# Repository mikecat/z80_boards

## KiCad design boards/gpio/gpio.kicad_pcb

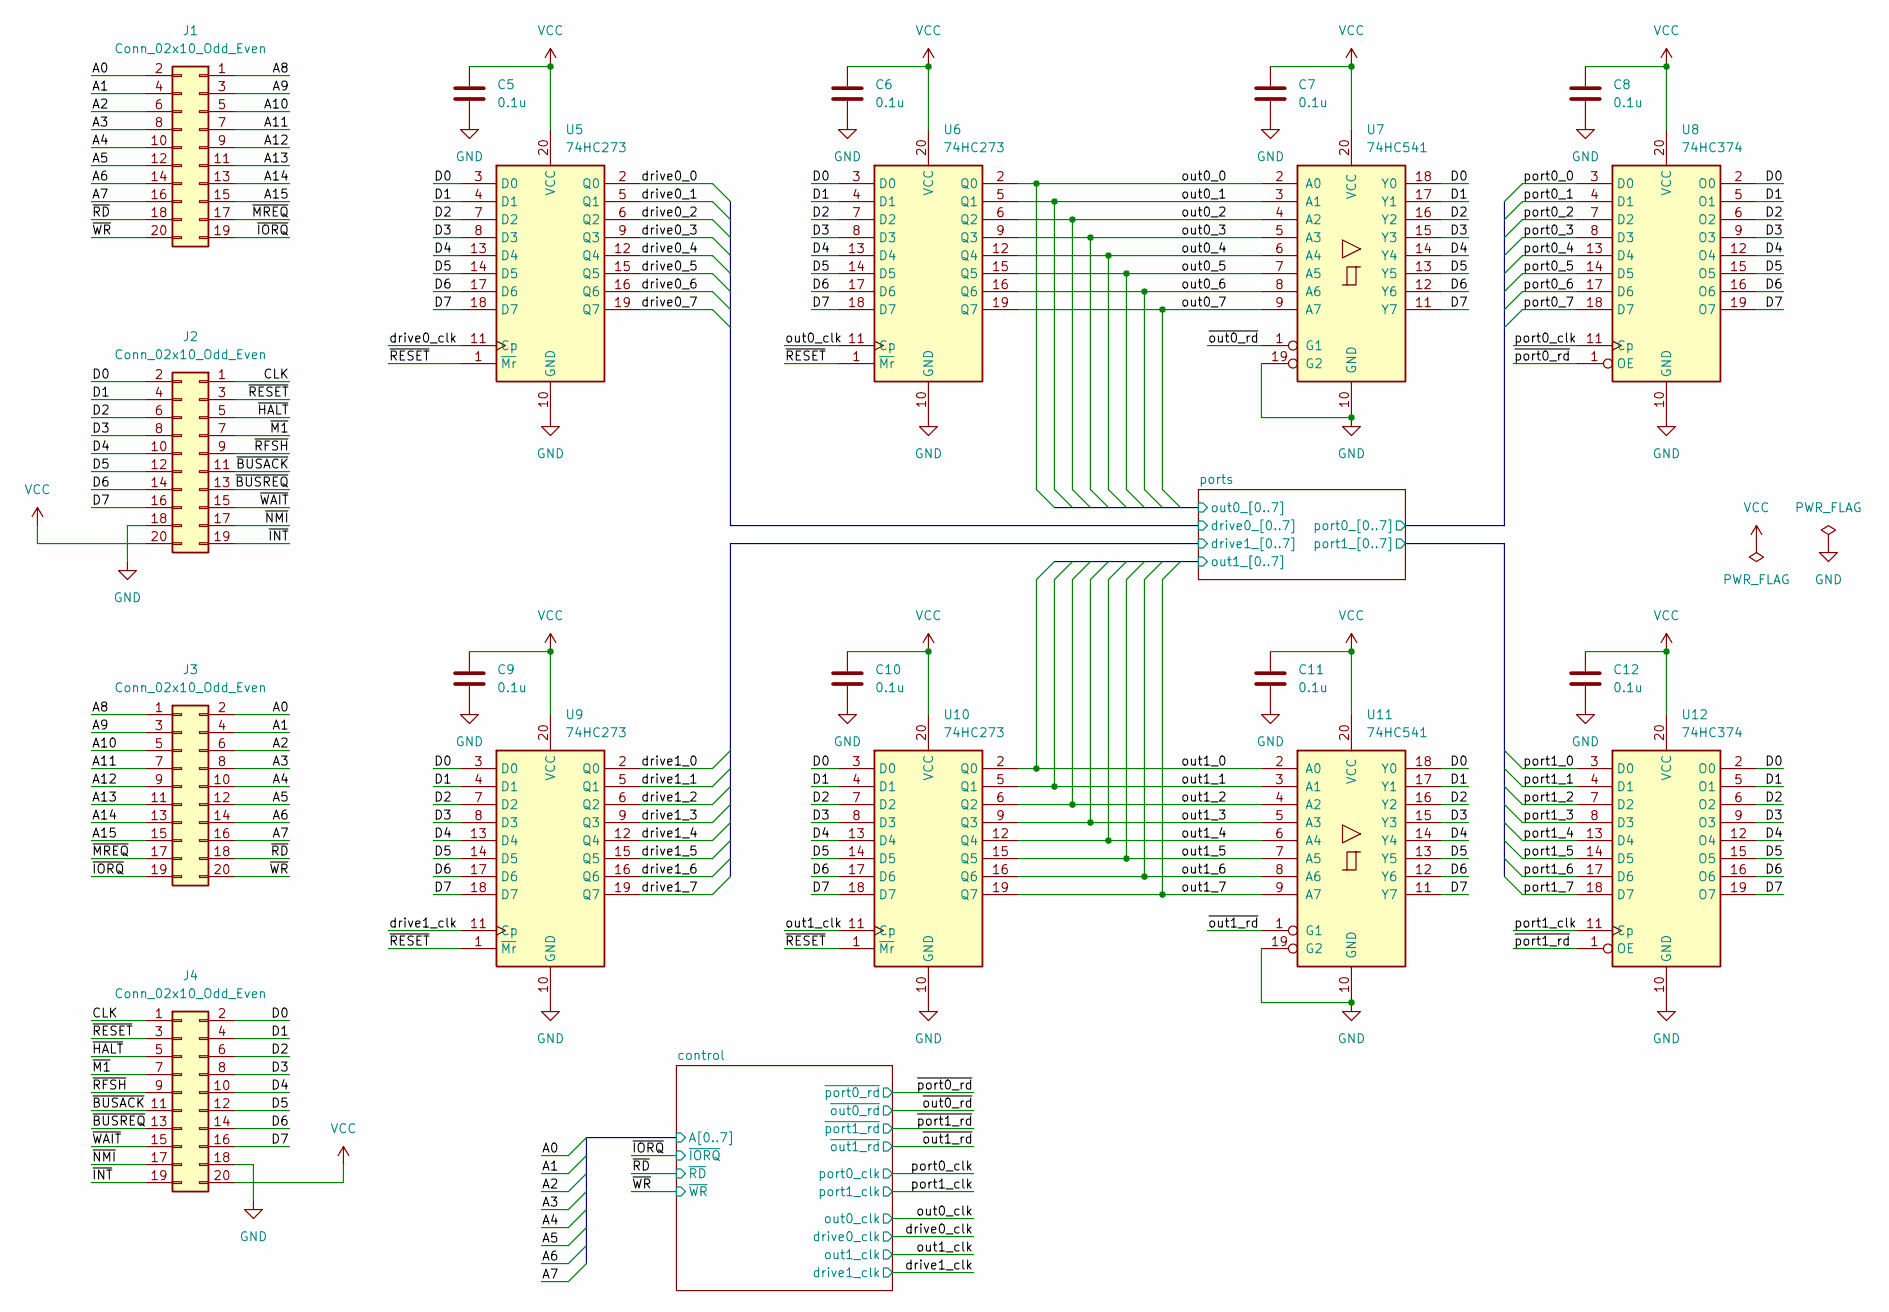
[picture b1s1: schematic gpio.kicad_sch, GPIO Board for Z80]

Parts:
C5, C6, C7, C8, C9, C10, C11, C12: 0.1u; C_0805_2012Metric_Pad1.18x1.45mm_HandSolder
J1, J2: Conn_02x10_Odd_Even; PinSocket_2x10_P2.54mm_Vertical
J3, J4: Conn_02x10_Odd_Even; PinHeader_2x10_P2.54mm_Vertical
U5, U6, U9, U10: 74HC273; DIP-20_W7.62mm
U7, U11: 74HC541; DIP-20_W7.62mm
U8, U12: 74HC374; DIP-20_W7.62mm

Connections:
/A8: J1.1, J3.1
/A9: J1.3, J3.3
/A10: J1.5, J3.5
/A11: J1.7, J3.7
/A12: J1.9, J3.9
/A13: J1.11, J3.11
/A14: J1.13, J3.13
/A15: J1.15, J3.15
/CLK: J2.1, J4.1
/D0: J2.2, J4.2, U5.3 (D0), U6.3 (D0), U7.18 (Y0), U8.2 (O0), U9.3 (D0), U10.3 (D0), U11.18 (Y0), U12.2 (O0)
/D1: J2.4, J4.4, U5.4 (D1), U6.4 (D1), U7.17 (Y1), U8.5 (O1), U9.4 (D1), U10.4 (D1), U11.17 (Y1), U12.5 (O1)
/D2: J2.6, J4.6, U5.7 (D2), U6.7 (D2), U7.16 (Y2), U8.6 (O2), U9.7 (D2), U10.7 (D2), U11.16 (Y2), U12.6 (O2)
/D3: J2.8, J4.8, U5.8 (D3), U6.8 (D3), U7.15 (Y3), U8.9 (O3), U9.8 (D3), U10.8 (D3), U11.15 (Y3), U12.9 (O3)
/D4: J2.10, J4.10, U5.13 (D4), U6.13 (D4), U7.14 (Y4), U8.12 (O4), U9.13 (D4), U10.13 (D4), U11.14 (Y4), U12.12 (O4)
/D5: J2.12, J4.12, U5.14 (D5), U6.14 (D5), U7.13 (Y5), U8.15 (O5), U9.14 (D5), U10.14 (D5), U11.13 (Y5), U12.15 (O5)
/D6: J2.14, J4.14, U5.17 (D6), U6.17 (D6), U7.12 (Y6), U8.16 (O6), U9.17 (D6), U10.17 (D6), U11.12 (Y6), U12.16 (O6)
/D7: J2.16, J4.16, U5.18 (D7), U6.18 (D7), U7.11 (Y7), U8.19 (O7), U9.18 (D7), U10.18 (D7), U11.11 (Y7), U12.19 (O7)
/control/A0: J1.2, J3.2; also elsewhere on the board
/control/A1: J1.4, J3.4; also elsewhere on the board
/control/A2: J1.6, J3.6; also elsewhere on the board
/control/A3: J1.8, J3.8; also elsewhere on the board
/control/A4: J1.10, J3.10; also elsewhere on the board
/control/A5: J1.12, J3.12; also elsewhere on the board
/control/A6: J1.14, J3.14; also elsewhere on the board
/control/A7: J1.16, J3.16; also elsewhere on the board
/drive0_clk: U5.11 (Cp); also elsewhere on the board
/drive1_clk: U9.11 (Cp); also elsewhere on the board
/out0_clk: U6.11 (Cp); also elsewhere on the board
/out1_clk: U10.11 (Cp); also elsewhere on the board
/port0_clk: U8.11 (Cp); also elsewhere on the board
/port1_clk: U12.11 (Cp); also elsewhere on the board
/ports/drive0_0: U5.2 (Q0); also elsewhere on the board
/ports/drive0_1: U5.5 (Q1); also elsewhere on the board
/ports/drive0_2: U5.6 (Q2); also elsewhere on the board
/ports/drive0_3: U5.9 (Q3); also elsewhere on the board
/ports/drive0_4: U5.12 (Q4); also elsewhere on the board
/ports/drive0_5: U5.15 (Q5); also elsewhere on the board
/ports/drive0_6: U5.16 (Q6); also elsewhere on the board
/ports/drive0_7: U5.19 (Q7); also elsewhere on the board
/ports/drive1_0: U9.2 (Q0); also elsewhere on the board
/ports/drive1_1: U9.5 (Q1); also elsewhere on the board
/ports/drive1_2: U9.6 (Q2); also elsewhere on the board
/ports/drive1_3: U9.9 (Q3); also elsewhere on the board
/ports/drive1_4: U9.12 (Q4); also elsewhere on the board
/ports/drive1_5: U9.15 (Q5); also elsewhere on the board
/ports/drive1_6: U9.16 (Q6); also elsewhere on the board
/ports/drive1_7: U9.19 (Q7); also elsewhere on the board
/ports/out0_0: U6.2 (Q0), U7.2 (A0); also elsewhere on the board
/ports/out0_1: U6.5 (Q1), U7.3 (A1); also elsewhere on the board
/ports/out0_2: U6.6 (Q2), U7.4 (A2); also elsewhere on the board
/ports/out0_3: U6.9 (Q3), U7.5 (A3); also elsewhere on the board
/ports/out0_4: U6.12 (Q4), U7.6 (A4); also elsewhere on the board
/ports/out0_5: U6.15 (Q5), U7.7 (A5); also elsewhere on the board
/ports/out0_6: U6.16 (Q6), U7.8 (A6); also elsewhere on the board
/ports/out0_7: U6.19 (Q7), U7.9 (A7); also elsewhere on the board
/ports/out1_0: U10.2 (Q0), U11.2 (A0); also elsewhere on the board
/ports/out1_1: U10.5 (Q1), U11.3 (A1); also elsewhere on the board
/ports/out1_2: U10.6 (Q2), U11.4 (A2); also elsewhere on the board
/ports/out1_3: U10.9 (Q3), U11.5 (A3); also elsewhere on the board
/ports/out1_4: U10.12 (Q4), U11.6 (A4); also elsewhere on the board
/ports/out1_5: U10.15 (Q5), U11.7 (A5); also elsewhere on the board
/ports/out1_6: U10.16 (Q6), U11.8 (A6); also elsewhere on the board
/ports/out1_7: U10.19 (Q7), U11.9 (A7); also elsewhere on the board
/ports/port0_0: U8.3 (D0); also elsewhere on the board
/ports/port0_1: U8.4 (D1); also elsewhere on the board
/ports/port0_2: U8.7 (D2); also elsewhere on the board
/ports/port0_3: U8.8 (D3); also elsewhere on the board
/ports/port0_4: U8.13 (D4); also elsewhere on the board
/ports/port0_5: U8.14 (D5); also elsewhere on the board
/ports/port0_6: U8.17 (D6); also elsewhere on the board
/ports/port0_7: U8.18 (D7); also elsewhere on the board
/ports/port1_0: U12.3 (D0); also elsewhere on the board
/ports/port1_1: U12.4 (D1); also elsewhere on the board
/ports/port1_2: U12.7 (D2); also elsewhere on the board
/ports/port1_3: U12.8 (D3); also elsewhere on the board
/ports/port1_4: U12.13 (D4); also elsewhere on the board
/ports/port1_5: U12.14 (D5); also elsewhere on the board
/ports/port1_6: U12.17 (D6); also elsewhere on the board
/ports/port1_7: U12.18 (D7); also elsewhere on the board
/~BUSACK: J2.11, J4.11
/~BUSREQ: J2.13, J4.13
/~HALT: J2.5, J4.5
/~INT: J2.19, J4.19
/~IORQ: J1.19, J3.19; also elsewhere on the board
/~M1: J2.7, J4.7
/~MREQ: J1.17, J3.17
/~NMI: J2.17, J4.17
/~RD: J1.18, J3.18; also elsewhere on the board
/~RESET: J2.3, J4.3, U5.1 (~Mr), U6.1 (~Mr), U9.1 (~Mr), U10.1 (~Mr)
/~RFSH: J2.9, J4.9
/~WAIT: J2.15, J4.15
/~WR: J1.20, J3.20; also elsewhere on the board
/~out0_rd: U7.1 (G1); also elsewhere on the board
/~out1_rd: U11.1 (G1); also elsewhere on the board
/~port0_rd: U8.1 (OE); also elsewhere on the board
/~port1_rd: U12.1 (OE); also elsewhere on the board
GND: C5.2, C6.2, C7.2, C8.2, C9.2, C10.2, C11.2, C12.2, J2.18, J4.18, U5.10 (GND), U6.10 (GND), U7.10 (GND), U7.19 (G2), U8.10 (GND), U9.10 (GND), U10.10 (GND), U11.10 (GND), U11.19 (G2), U12.10 (GND); also elsewhere on the board
VCC: C5.1, C6.1, C7.1, C8.1, C9.1, C10.1, C11.1, C12.1, J2.20, J4.20, U5.20 (VCC), U6.20 (VCC), U7.20 (VCC), U8.20 (VCC), U9.20 (VCC), U10.20 (VCC), U11.20 (VCC), U12.20 (VCC); also elsewhere on the board

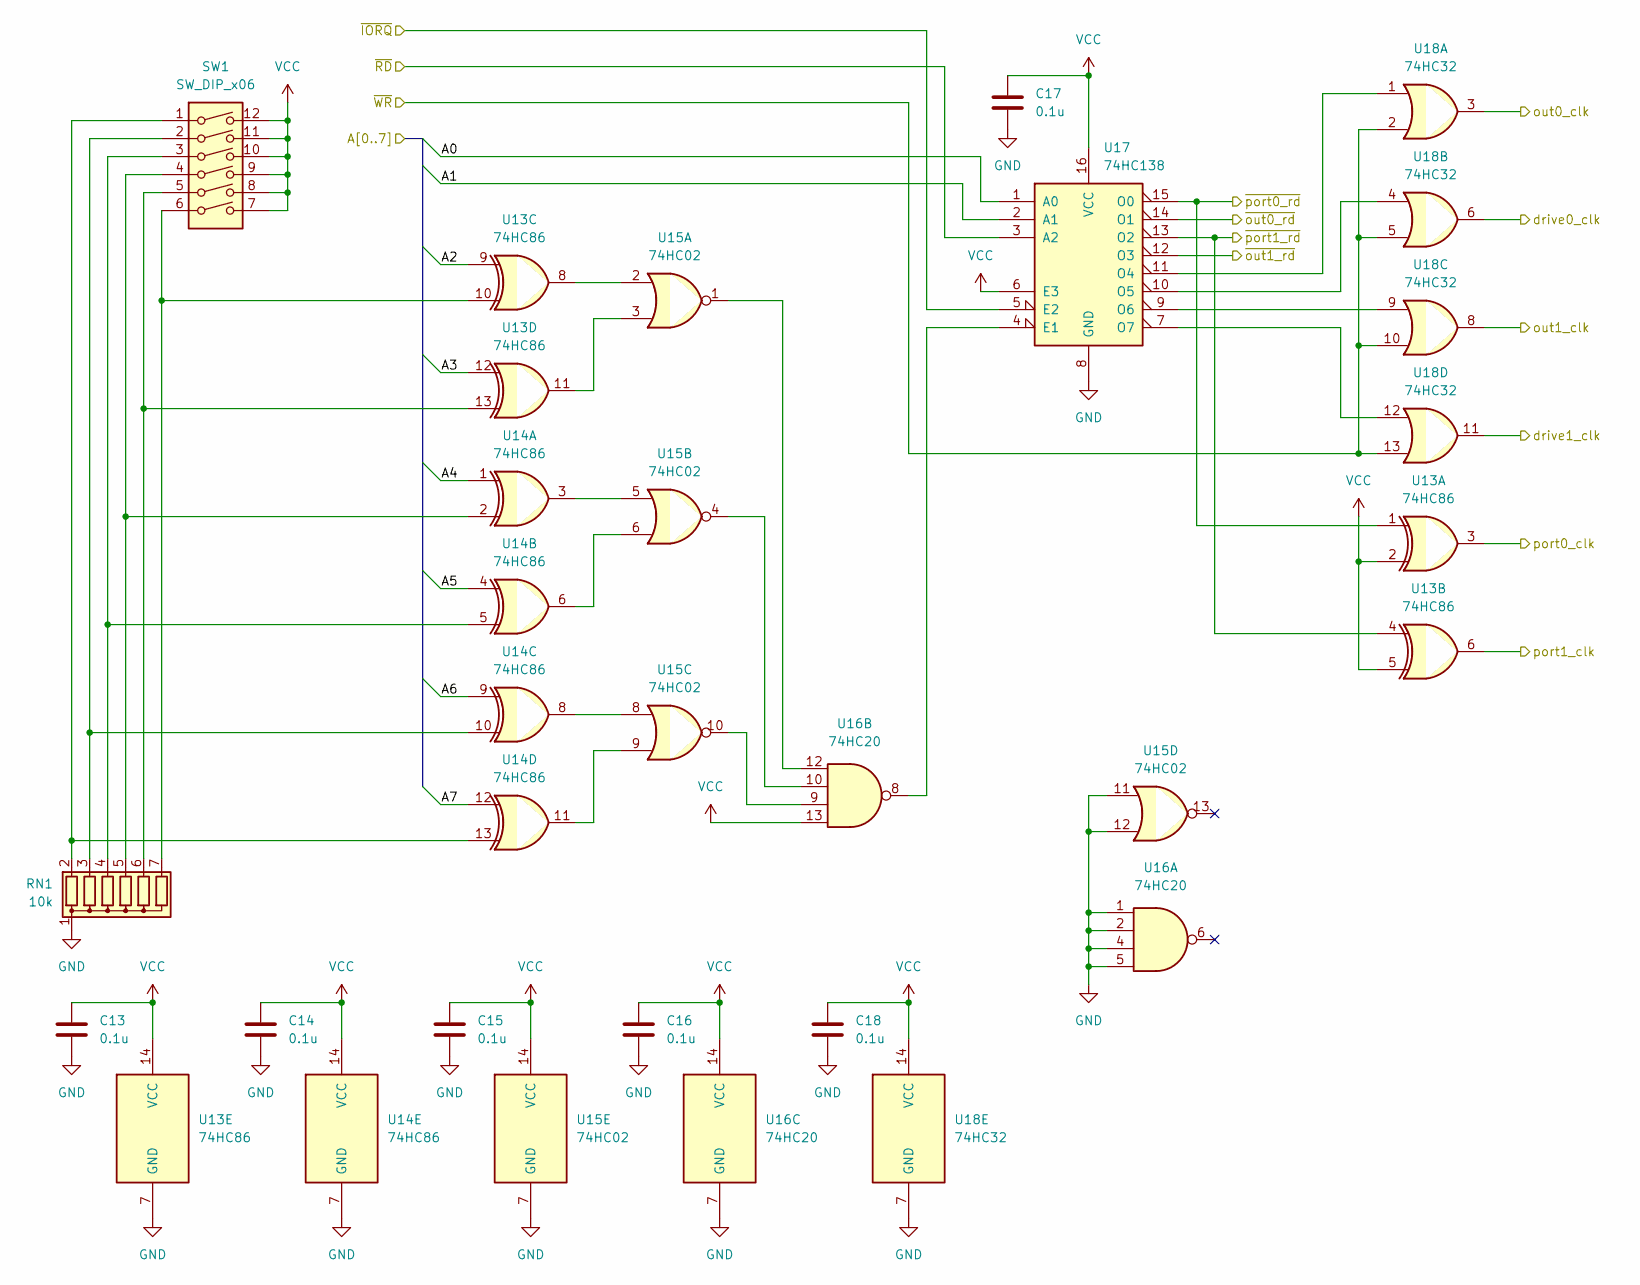
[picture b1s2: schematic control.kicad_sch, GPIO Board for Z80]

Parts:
C13, C14, C15, C16, C17, C18: 0.1u; C_0805_2012Metric_Pad1.18x1.45mm_HandSolder
RN1: 10k; R_Array_SIP7
SW1: SW_DIP_x06; SW_DIP_SPSTx06_Slide_9.78x17.42mm_W7.62mm_P2.54mm
U13, U14: 74HC86; DIP-14_W7.62mm
U15: 74HC02; DIP-14_W7.62mm
U16: 74HC20; DIP-14_W7.62mm
U17: 74HC138; DIP-16_W7.62mm
U18: 74HC32; DIP-14_W7.62mm

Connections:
/control/A0: U17.1 (A0); also elsewhere on the board
/control/A1: U17.2 (A1); also elsewhere on the board
/control/A2: U13.9; also elsewhere on the board
/control/A3: U13.12; also elsewhere on the board
/control/A4: U14.1; also elsewhere on the board
/control/A5: U14.4; also elsewhere on the board
/control/A6: U14.9; also elsewhere on the board
/control/A7: U14.12; also elsewhere on the board
/drive0_clk: U18.6; also elsewhere on the board
/drive1_clk: U18.11; also elsewhere on the board
/out0_clk: U18.3; also elsewhere on the board
/out1_clk: U18.8; also elsewhere on the board
/port0_clk: U13.3; also elsewhere on the board
/port1_clk: U13.6; also elsewhere on the board
/~IORQ: U17.5 (E2); also elsewhere on the board
/~RD: U17.3 (A2); also elsewhere on the board
/~WR: U18.2, U18.5, U18.10, U18.13; also elsewhere on the board
/~out0_rd: U17.14 (O1); also elsewhere on the board
/~out1_rd: U17.12 (O3); also elsewhere on the board
/~port0_rd: U13.1, U17.15 (O0); also elsewhere on the board
/~port1_rd: U13.4, U17.13 (O2); also elsewhere on the board
GND: C13.2, C14.2, C15.2, C16.2, C17.2, C18.2, RN1.1 (common), U13.7 (GND), U14.7 (GND), U15.7 (GND), U15.11, U15.12, U16.1, U16.2, U16.4, U16.5, U16.7 (GND), U17.8 (GND), U18.7 (GND); also elsewhere on the board
unnamed: RN1.2 (R1), SW1.1, U14.13
unnamed: RN1.3 (R2), SW1.2, U14.10
unnamed: RN1.4 (R3), SW1.3, U14.5
unnamed: RN1.5 (R4), SW1.4, U14.2
unnamed: RN1.6 (R5), SW1.5, U13.13
unnamed: RN1.7 (R6), SW1.6, U13.10
unnamed: U13.8, U15.2
unnamed: U13.11, U15.3
unnamed: U14.3, U15.5
unnamed: U14.6, U15.6
unnamed: U14.8, U15.8
unnamed: U14.11, U15.9
unnamed: U15.1, U16.12
unnamed: U15.4, U16.10
unnamed: U15.10, U16.9
unnamed: U16.8, U17.4 (E1)
unnamed: U17.7 (O7), U18.12
unnamed: U17.9 (O6), U18.9
unnamed: U17.10 (O5), U18.4
unnamed: U17.11 (O4), U18.1
VCC: C13.1, C14.1, C15.1, C16.1, C17.1, C18.1, SW1.7, SW1.8, SW1.9, SW1.10, SW1.11, SW1.12, U13.2, U13.5, U13.14 (VCC), U14.14 (VCC), U15.14 (VCC), U16.13, U16.14 (VCC), U17.6 (E3), U17.16 (VCC), U18.14 (VCC); also elsewhere on the board

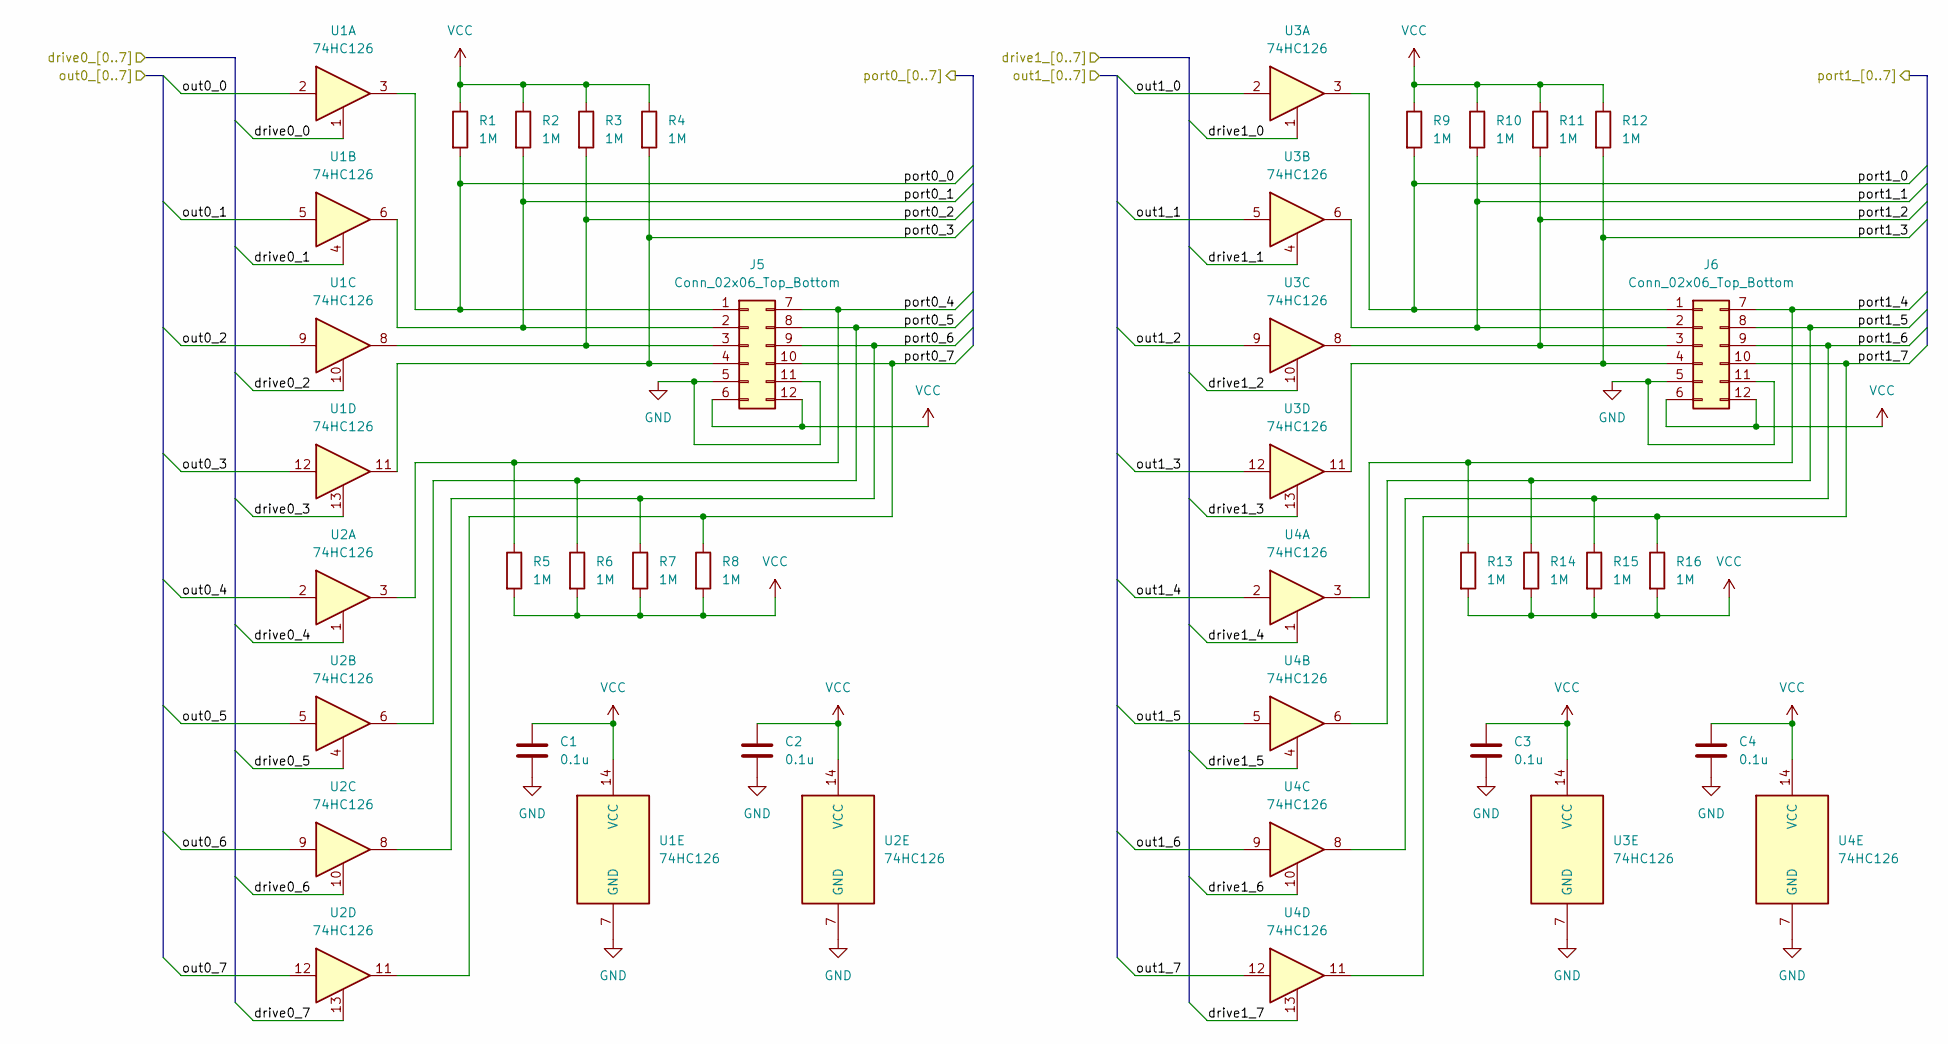
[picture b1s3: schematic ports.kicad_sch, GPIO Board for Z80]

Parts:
C1, C2, C3, C4: 0.1u; C_0805_2012Metric_Pad1.18x1.45mm_HandSolder
J5, J6: Conn_02x06_Top_Bottom; PinHeader_2x06_P2.54mm_Vertical
R1, R2, R3, R4, R5, R6, R7, R8, R9, R10, R11, R12, R13, R14, R15, R16: 1M; R_0805_2012Metric_Pad1.20x1.40mm_HandSolder
U1, U2, U3, U4: 74HC126; DIP-14_W7.62mm

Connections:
/ports/drive0_0: U1.1; also elsewhere on the board
/ports/drive0_1: U1.4; also elsewhere on the board
/ports/drive0_2: U1.10; also elsewhere on the board
/ports/drive0_3: U1.13; also elsewhere on the board
/ports/drive0_4: U2.1; also elsewhere on the board
/ports/drive0_5: U2.4; also elsewhere on the board
/ports/drive0_6: U2.10; also elsewhere on the board
/ports/drive0_7: U2.13; also elsewhere on the board
/ports/drive1_0: U3.1; also elsewhere on the board
/ports/drive1_1: U3.4; also elsewhere on the board
/ports/drive1_2: U3.10; also elsewhere on the board
/ports/drive1_3: U3.13; also elsewhere on the board
/ports/drive1_4: U4.1; also elsewhere on the board
/ports/drive1_5: U4.4; also elsewhere on the board
/ports/drive1_6: U4.10; also elsewhere on the board
/ports/drive1_7: U4.13; also elsewhere on the board
/ports/out0_0: U1.2; also elsewhere on the board
/ports/out0_1: U1.5; also elsewhere on the board
/ports/out0_2: U1.9; also elsewhere on the board
/ports/out0_3: U1.12; also elsewhere on the board
/ports/out0_4: U2.2; also elsewhere on the board
/ports/out0_5: U2.5; also elsewhere on the board
/ports/out0_6: U2.9; also elsewhere on the board
/ports/out0_7: U2.12; also elsewhere on the board
/ports/out1_0: U3.2; also elsewhere on the board
/ports/out1_1: U3.5; also elsewhere on the board
/ports/out1_2: U3.9; also elsewhere on the board
/ports/out1_3: U3.12; also elsewhere on the board
/ports/out1_4: U4.2; also elsewhere on the board
/ports/out1_5: U4.5; also elsewhere on the board
/ports/out1_6: U4.9; also elsewhere on the board
/ports/out1_7: U4.12; also elsewhere on the board
/ports/port0_0: J5.1, R1.2, U1.3; also elsewhere on the board
/ports/port0_1: J5.2, R2.2, U1.6; also elsewhere on the board
/ports/port0_2: J5.3, R3.2, U1.8; also elsewhere on the board
/ports/port0_3: J5.4, R4.2, U1.11; also elsewhere on the board
/ports/port0_4: J5.7, R5.1, U2.3; also elsewhere on the board
/ports/port0_5: J5.8, R6.1, U2.6; also elsewhere on the board
/ports/port0_6: J5.9, R7.1, U2.8; also elsewhere on the board
/ports/port0_7: J5.10, R8.1, U2.11; also elsewhere on the board
/ports/port1_0: J6.1, R9.2, U3.3; also elsewhere on the board
/ports/port1_1: J6.2, R10.2, U3.6; also elsewhere on the board
/ports/port1_2: J6.3, R11.2, U3.8; also elsewhere on the board
/ports/port1_3: J6.4, R12.2, U3.11; also elsewhere on the board
/ports/port1_4: J6.7, R13.1, U4.3; also elsewhere on the board
/ports/port1_5: J6.8, R14.1, U4.6; also elsewhere on the board
/ports/port1_6: J6.9, R15.1, U4.8; also elsewhere on the board
/ports/port1_7: J6.10, R16.1, U4.11; also elsewhere on the board
GND: C1.2, C2.2, C3.2, C4.2, J5.5, J5.11, J6.5, J6.11, U1.7 (GND), U2.7 (GND), U3.7 (GND), U4.7 (GND); also elsewhere on the board
VCC: C1.1, C2.1, C3.1, C4.1, J5.6, J5.12, J6.6, J6.12, R1.1, R2.1, R3.1, R4.1, R5.2, R6.2, R7.2, R8.2, R9.1, R10.1, R11.1, R12.1, R13.2, R14.2, R15.2, R16.2, U1.14 (VCC), U2.14 (VCC), U3.14 (VCC), U4.14 (VCC); also elsewhere on the board

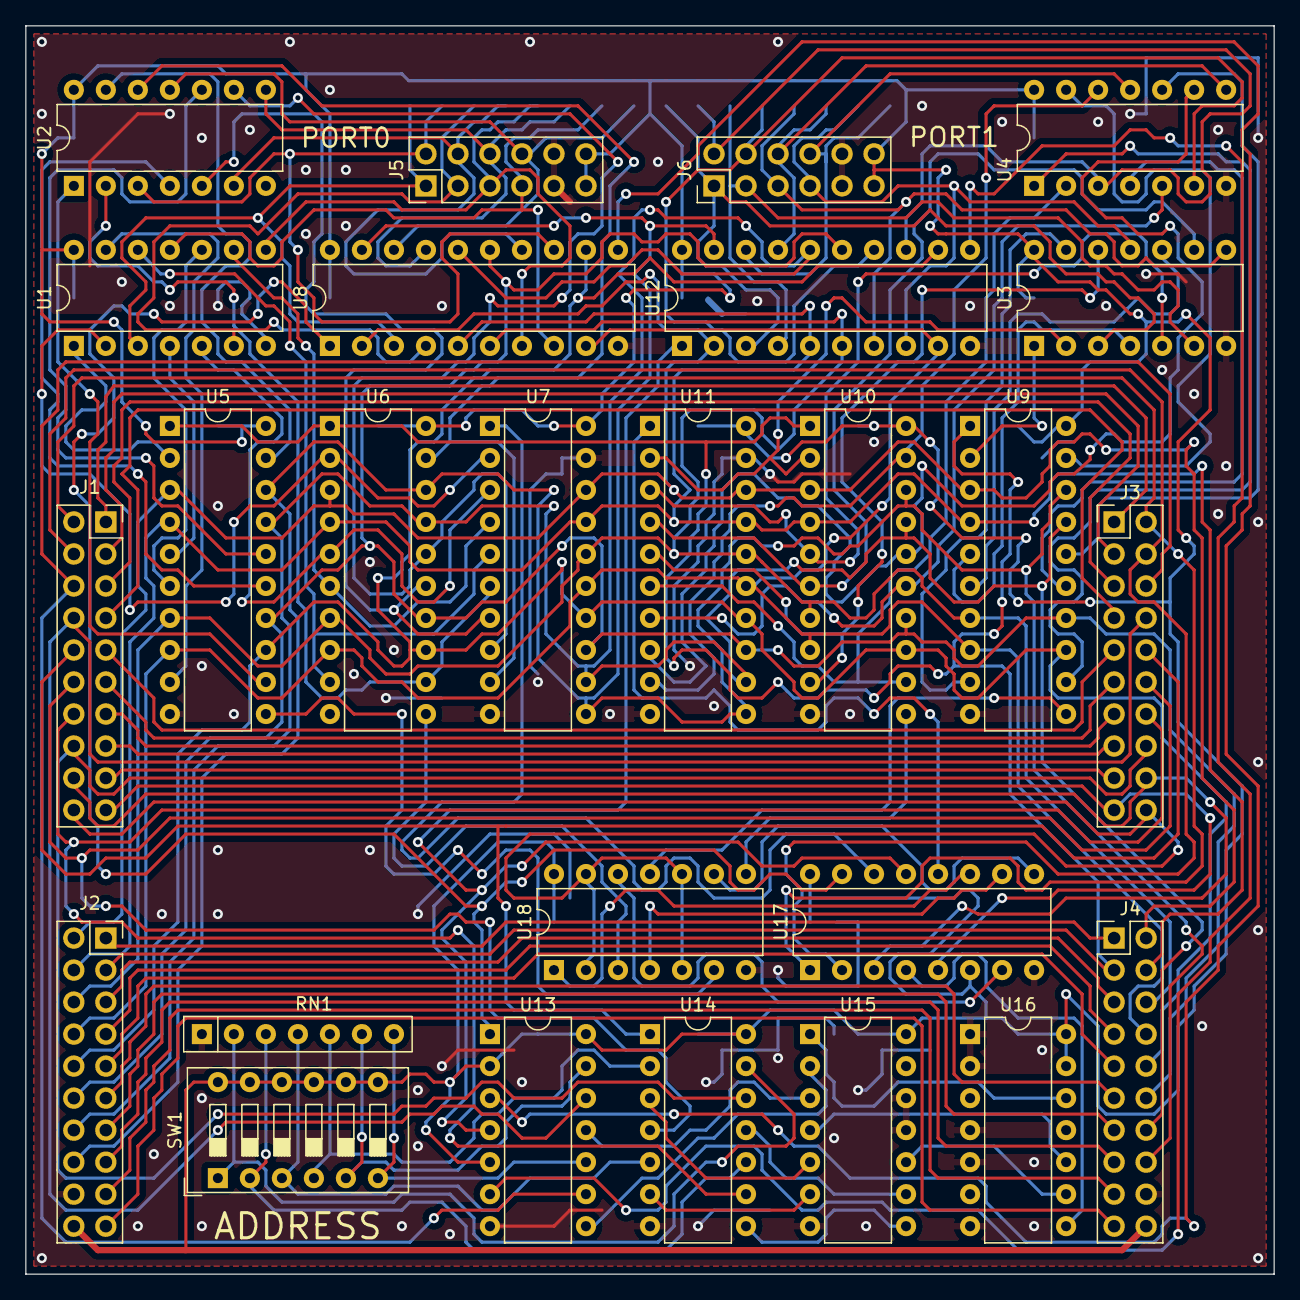
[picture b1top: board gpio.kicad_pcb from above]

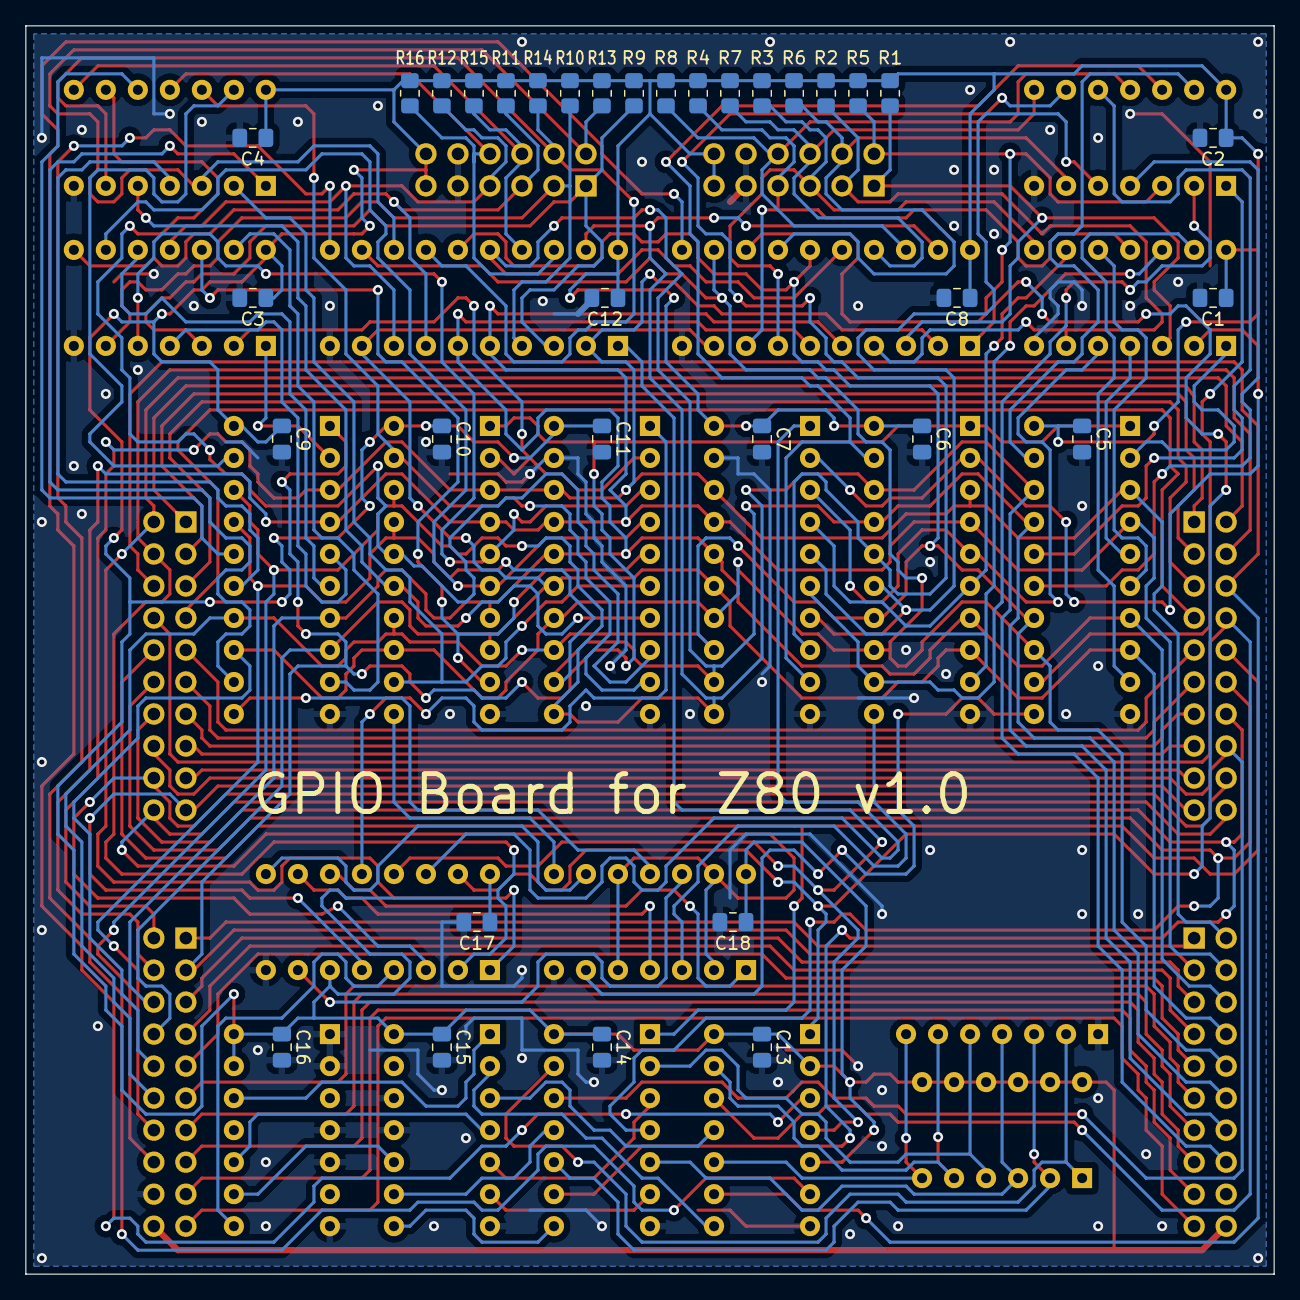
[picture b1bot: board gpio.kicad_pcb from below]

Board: 2 copper layers, 99.1 x 99.1 mm, 60 parts (34 on the bottom side), 118 nets.

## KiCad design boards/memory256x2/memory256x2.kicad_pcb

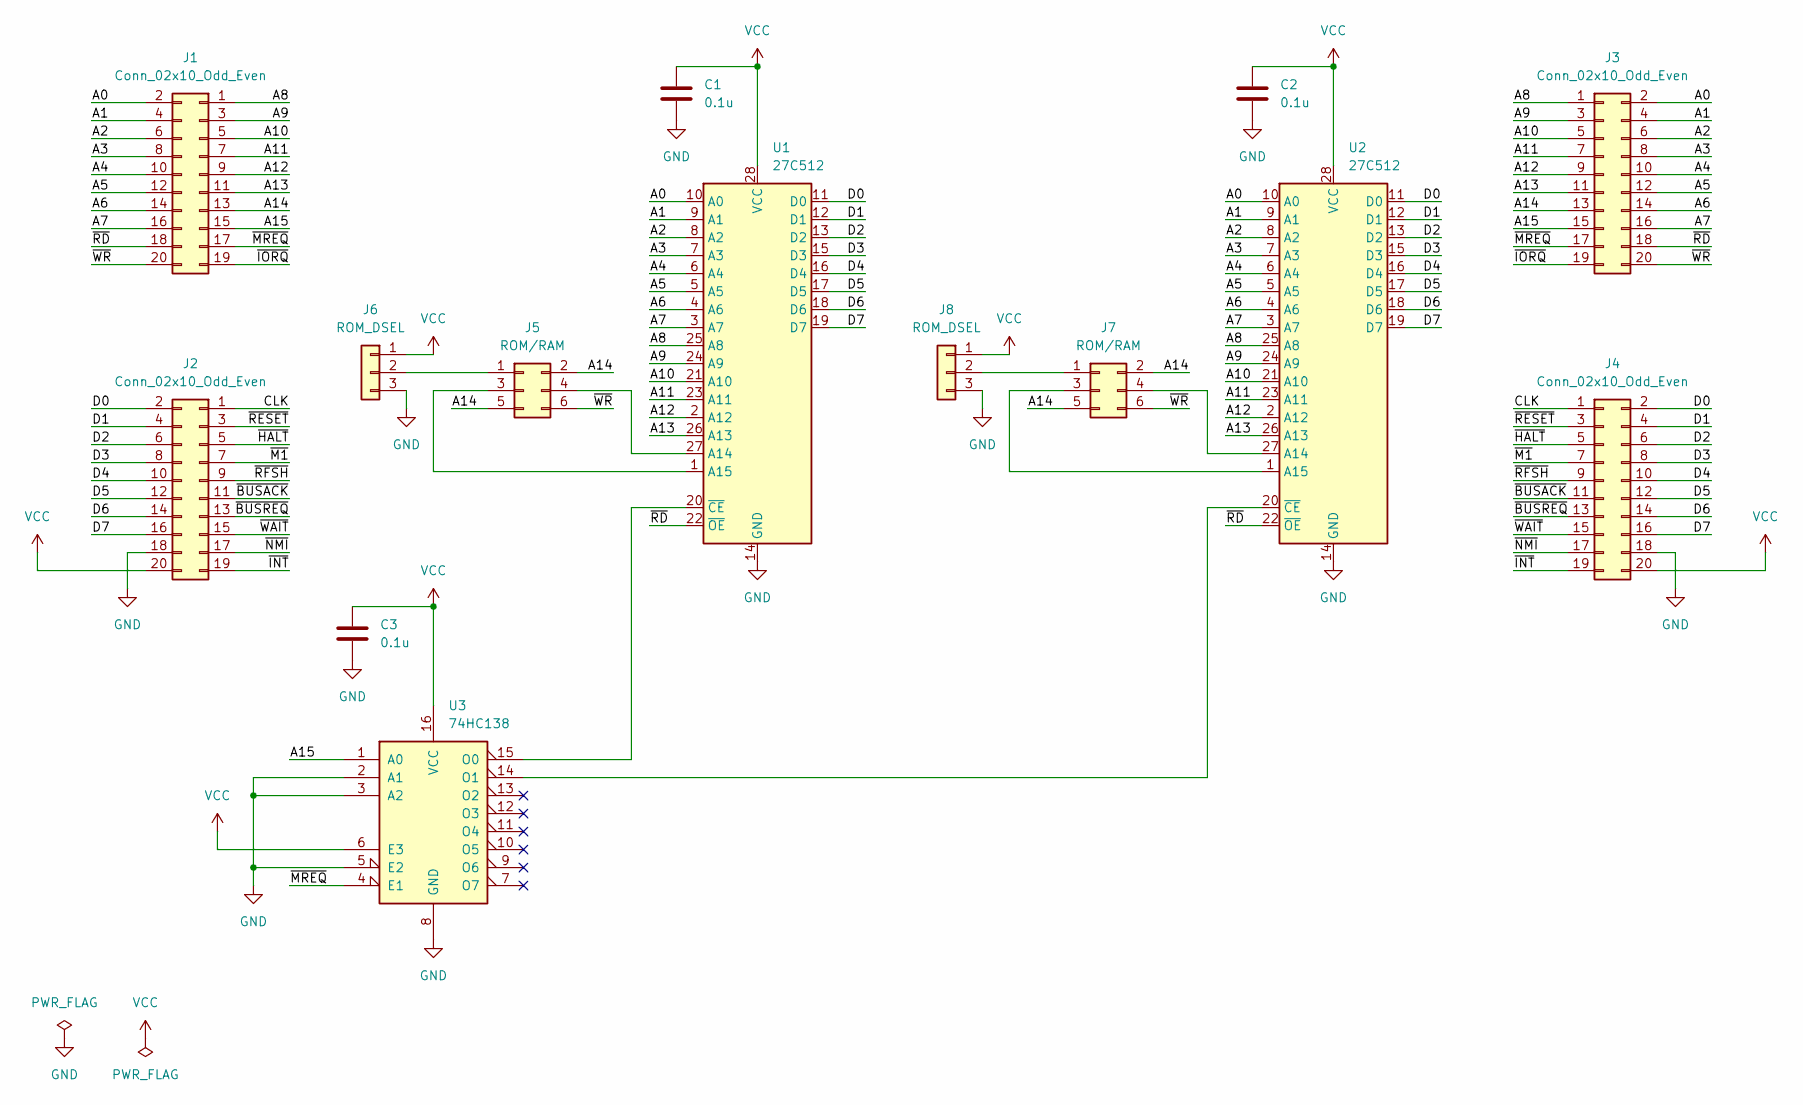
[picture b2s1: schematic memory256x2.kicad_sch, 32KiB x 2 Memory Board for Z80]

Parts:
C1, C2, C3: 0.1u; C_0805_2012Metric_Pad1.18x1.45mm_HandSolder
J1, J2: Conn_02x10_Odd_Even; PinSocket_2x10_P2.54mm_Vertical
J3, J4: Conn_02x10_Odd_Even; PinHeader_2x10_P2.54mm_Vertical
J5, J7: ROM/RAM; PinHeader_2x03_P2.54mm_Vertical
J6, J8: ROM_DSEL; PinHeader_1x03_P2.54mm_Vertical
U1, U2: 27C512; DIP-28_W15.24mm
U3: 74HC138; DIP-16_W7.62mm

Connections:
/A0: J1.2, J3.2, U1.10 (A0), U2.10 (A0)
/A1: J1.4, J3.4, U1.9 (A1), U2.9 (A1)
/A2: J1.6, J3.6, U1.8 (A2), U2.8 (A2)
/A3: J1.8, J3.8, U1.7 (A3), U2.7 (A3)
/A4: J1.10, J3.10, U1.6 (A4), U2.6 (A4)
/A5: J1.12, J3.12, U1.5 (A5), U2.5 (A5)
/A6: J1.14, J3.14, U1.4 (A6), U2.4 (A6)
/A7: J1.16, J3.16, U1.3 (A7), U2.3 (A7)
/A8: J1.1, J3.1, U1.25 (A8), U2.25 (A8)
/A9: J1.3, J3.3, U1.24 (A9), U2.24 (A9)
/A10: J1.5, J3.5, U1.21 (A10), U2.21 (A10)
/A11: J1.7, J3.7, U1.23 (A11), U2.23 (A11)
/A12: J1.9, J3.9, U1.2 (A12), U2.2 (A12)
/A13: J1.11, J3.11, U1.26 (A13), U2.26 (A13)
/A14: J1.13, J3.13, J5.2, J5.5, J7.2, J7.5
/A15: J1.15, J3.15, U3.1 (A0)
/CLK: J2.1, J4.1
/D0: J2.2, J4.2, U1.11 (D0), U2.11 (D0)
/D1: J2.4, J4.4, U1.12 (D1), U2.12 (D1)
/D2: J2.6, J4.6, U1.13 (D2), U2.13 (D2)
/D3: J2.8, J4.8, U1.15 (D3), U2.15 (D3)
/D4: J2.10, J4.10, U1.16 (D4), U2.16 (D4)
/D5: J2.12, J4.12, U1.17 (D5), U2.17 (D5)
/D6: J2.14, J4.14, U1.18 (D6), U2.18 (D6)
/D7: J2.16, J4.16, U1.19 (D7), U2.19 (D7)
/~BUSACK: J2.11, J4.11
/~BUSREQ: J2.13, J4.13
/~HALT: J2.5, J4.5
/~INT: J2.19, J4.19
/~IORQ: J1.19, J3.19
/~M1: J2.7, J4.7
/~MREQ: J1.17, J3.17, U3.4 (E1)
/~NMI: J2.17, J4.17
/~RD: J1.18, J3.18, U1.22 (~OE), U2.22 (~OE)
/~RESET: J2.3, J4.3
/~RFSH: J2.9, J4.9
/~WAIT: J2.15, J4.15
/~WR: J1.20, J3.20, J5.6, J7.6
GND: C1.2, C2.2, C3.2, J2.18, J4.18, J6.3, J8.3, U1.14 (GND), U2.14 (GND), U3.2 (A1), U3.3 (A2), U3.5 (E2), U3.8 (GND)
unnamed: J5.1, J6.2
unnamed: J5.3, U1.1 (A15)
unnamed: J5.4, U1.27 (A14)
unnamed: J7.1, J8.2
unnamed: J7.3, U2.1 (A15)
unnamed: J7.4, U2.27 (A14)
unnamed: U1.20 (~CE), U3.15 (O0)
unnamed: U2.20 (~CE), U3.14 (O1)
VCC: C1.1, C2.1, C3.1, J2.20, J4.20, J6.1, J8.1, U1.28 (VCC), U2.28 (VCC), U3.6 (E3), U3.16 (VCC)

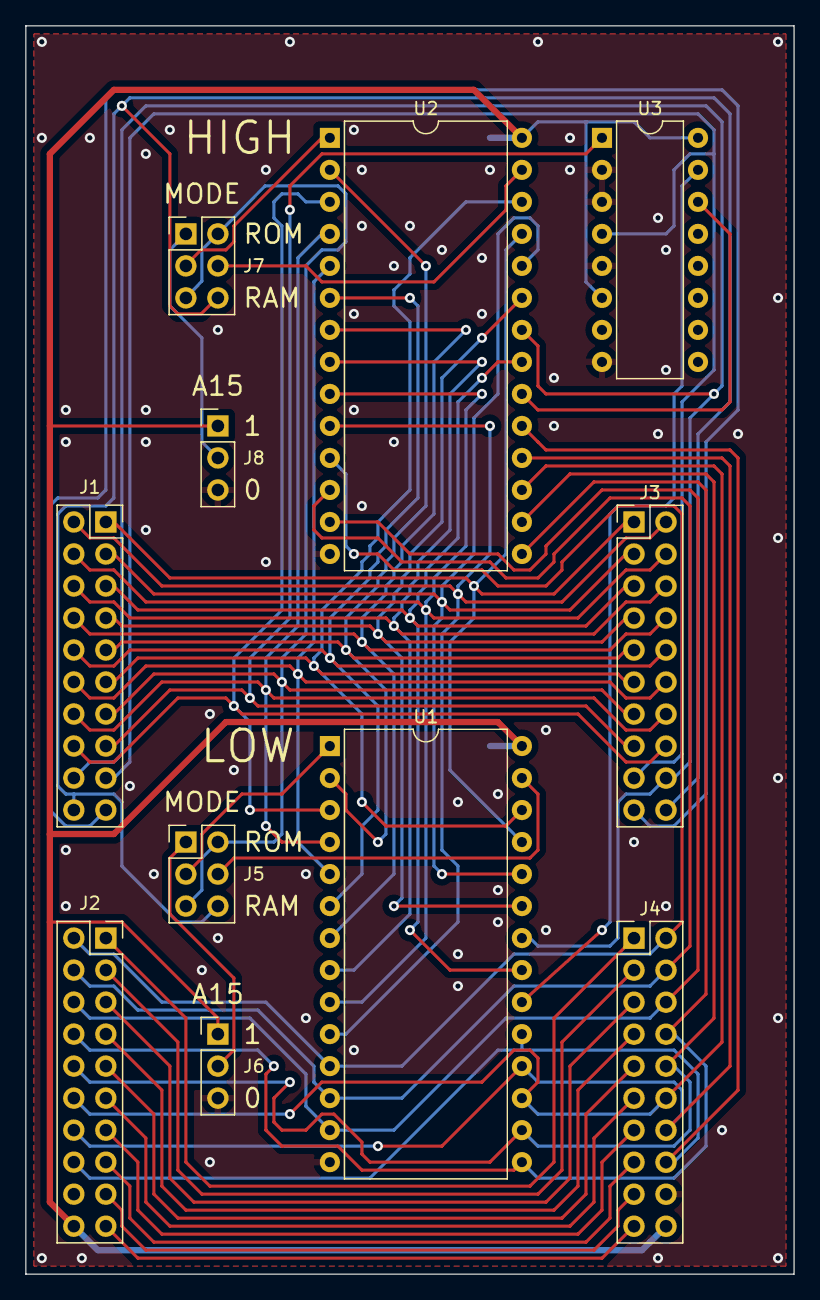
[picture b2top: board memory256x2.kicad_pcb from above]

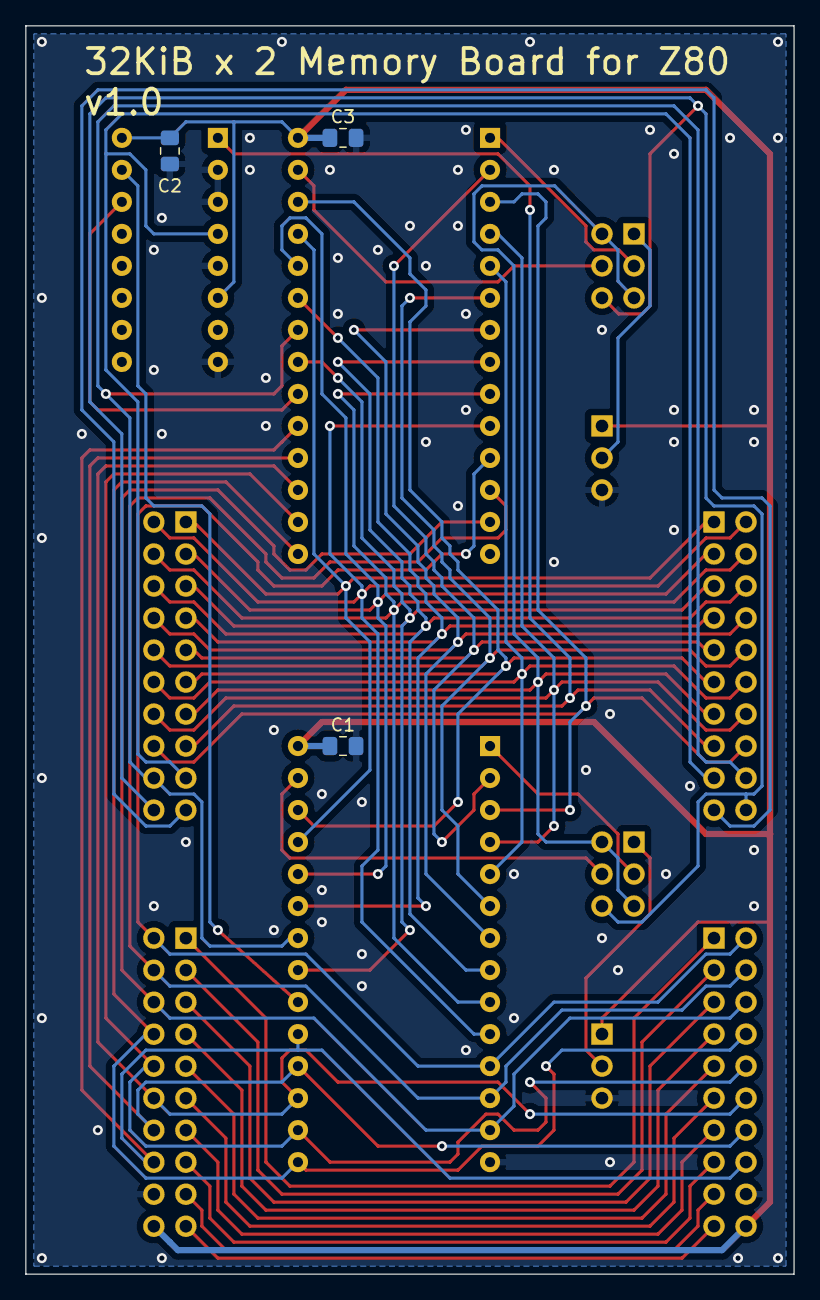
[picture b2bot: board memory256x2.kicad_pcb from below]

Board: 2 copper layers, 61.0 x 99.1 mm, 14 parts (3 on the bottom side), 48 nets.
